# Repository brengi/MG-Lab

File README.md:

# MG-Lab
Producción del Laboratorio Mario Gattafoni

## Objetivos ##
El MG-Lab trabaja con alumnos de colegios técnicos secundarios, bajo
el régimen de práctica profesional supervisada.
Se utilizan tecnologías abiertas y se publican los resultados de cada
práctica.

## Responsables ##
El plantel estable del laboratorio esta formado por Omar Milano y Diego Brengi.

## Nombre del laboratorio ##
El laboratorio se bautiza con ese nombre en honor a Mario Gattafoni quien fue profesor
de Omar y Diego en la secundaria y en la universidad, y dedicó su vida a 
la educación técnica secundaria y universitaria.

## Grupos MG-LAB 2019

De izquierda a derecha:.

De izquierda a derecha:.

De izquierda a derecha:.

## Grupos MG-LAB 2018

De izquierda a derecha: Omar Milano, ... y Diego Brengi.

## Grupos MG-LAB 2017

De izquierda a derecha: Omar Milano, Delfina Gonzalez, Gonzalo Daniel Magdalena, Nelson Saade y Diego Brengi.

De izquierda a derecha: Diego Brengi, XX1, XX2, XX3 y Omar Milano.

## Grupos MG-LAB 2016

De izquierda a derecha: Diego Brengi, Juan Ignacio
Napolillo, Nicolas David Luna, Omar Milano y Leonel Gabriel Costa.

De izquierda a derecha: Diego Brengi, Alejandro Franco, Fernando Flores, Omar Milano y Fernando Sosa.

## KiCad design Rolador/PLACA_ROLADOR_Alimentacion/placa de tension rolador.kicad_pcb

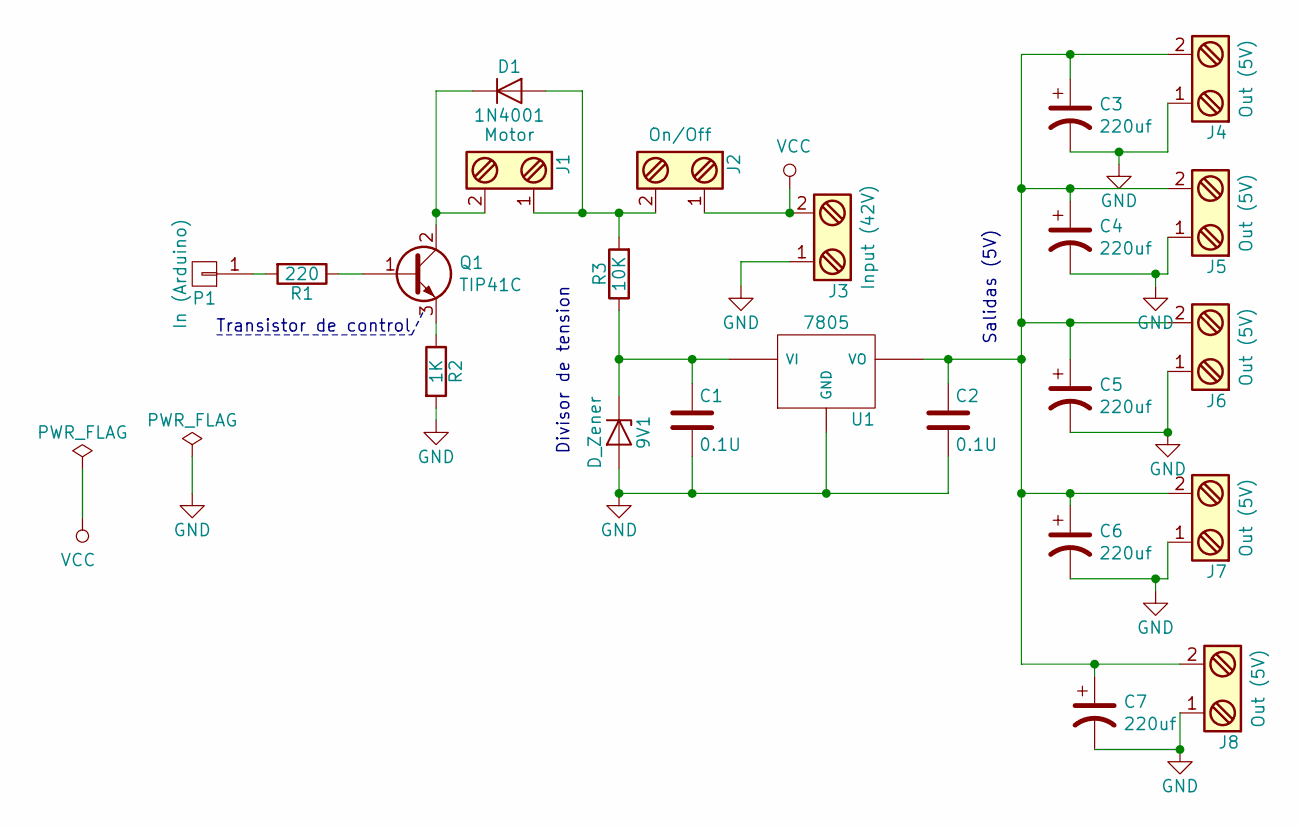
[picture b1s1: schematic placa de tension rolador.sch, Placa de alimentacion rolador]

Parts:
9V1: D_Zener; D_DO-41_SOD81_P12.70mm_Horizontal
C1, C2: 0.1U; C_Rect_L7.0mm_W6.0mm_P5.00mm
C3, C4, C5, C6, C7: 220uf; CP_Radial_D8.0mm_P3.80mm
D1: 1N4001; D_DO-41_SOD81_P12.70mm_Horizontal
J1: Motor; TerminalBlock_bornier-2_P5.08mm
J2: On/Off; TerminalBlock_bornier-2_P5.08mm
J3: Input (42V); TerminalBlock_bornier-2_P5.08mm
J4, J5, J6, J7, J8: Out (5V); TerminalBlock_bornier-2_P5.08mm
P1: In (Arduino); Pin_D0.7mm_L6.5mm_W1.8mm_FlatFork
Q1: TIP41C; TO-220-3_Vertical
R1: 220; R_Axial_DIN0207_L6.3mm_D2.5mm_P10.16mm_Horizontal
R2: 1K; R_Axial_DIN0207_L6.3mm_D2.5mm_P10.16mm_Horizontal
R3: 10K; R_Axial_DIN0207_L6.3mm_D2.5mm_P10.16mm_Horizontal
U1: 7805; TO-220-3_Vertical

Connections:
GND: 9V1.2 (A), C1.2, C2.2, C3.2, C4.2, C5.2, C6.2, C7.2, J3.1, J4.1, J5.1, J6.1, J7.1, J8.1, R2.2, U1.2 (GND)
unnamed: 9V1.1 (K), C1.1, R3.1, U1.1 (VI)
unnamed: C2.1, C3.1, C4.1, C5.1, C6.1, C7.1, J4.2, J5.2, J6.2, J7.2, J8.2, U1.3 (VO)
unnamed: D1.1 (K), J1.2, Q1.2 (C)
unnamed: D1.2 (A), J1.1, J2.2, R3.2
unnamed: P1.1, R1.2
unnamed: Q1.1 (B), R1.1
unnamed: Q1.3 (E), R2.1
VCC: J2.1, J3.2

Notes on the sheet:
Transistor de control
Divisor de tension
Salidas (5V)

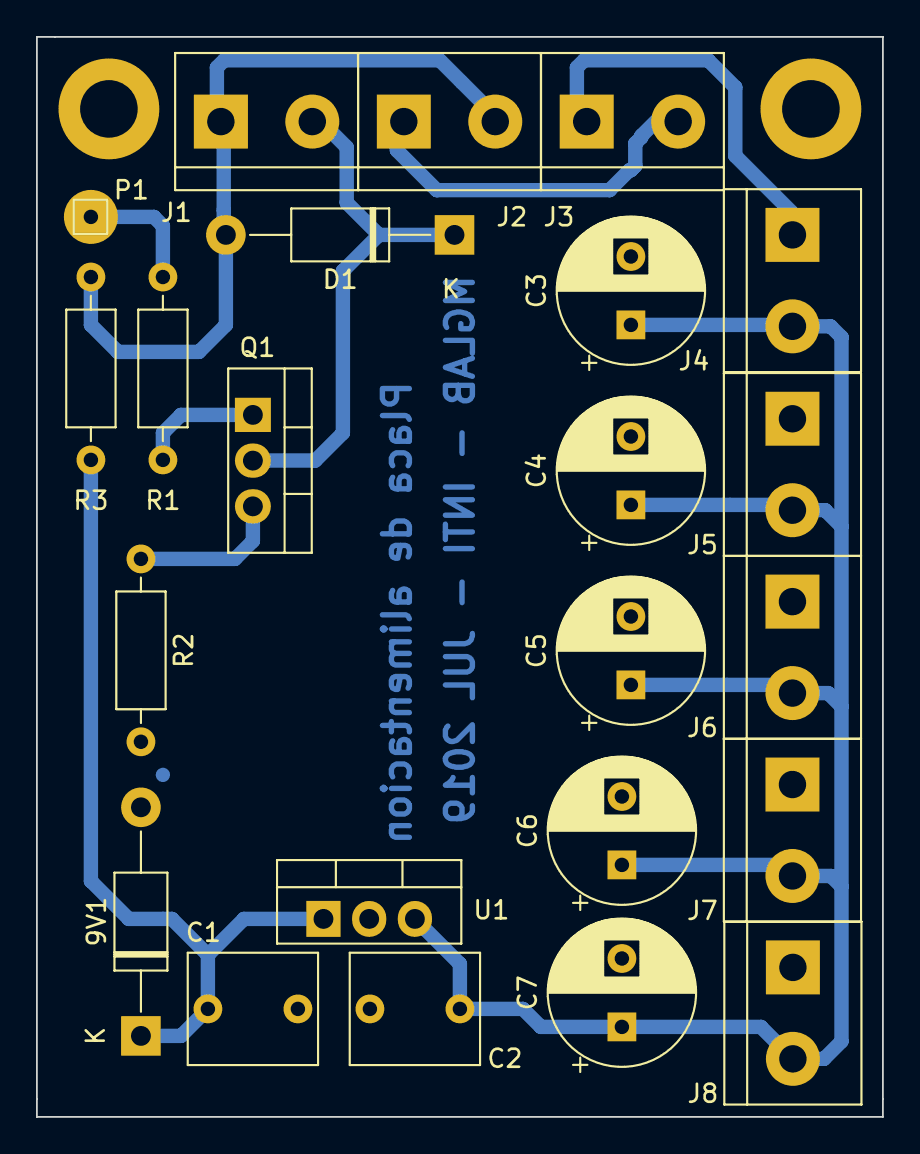
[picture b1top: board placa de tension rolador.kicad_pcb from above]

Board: 2 copper layers, 47.0 x 60.0 mm, 25 parts (0 on the bottom side), 9 nets.

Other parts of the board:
H1, H2: .; MountingHole_3.2mm_M3_DIN965_Pad

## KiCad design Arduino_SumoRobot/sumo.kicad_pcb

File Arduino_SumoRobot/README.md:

# SHIELD DE ARDUINO PARA ROBOT SUMO #
 
RESPONSABLE:  
 
## ACTIVIDAD ##
Realizar un una implementación con Arduino que permita controlar un robot 
sumo. Primero con módulos comerciales y cableado y luego si es posible, diseñar uno o 
más shields usando KiCad.
 
## PAUTAS ##
  *  Manejo de dos motores en ambos sentidos, con relés. 
  * Manejo de 4 sensores de línea infrarrojos. 
  * Entrada de dos pulsadores. 
  * Manejo de un relé o salida transistor adicional y posibilidad de manejar un servo 
(puede ser todo el mismo pin). 
  * Posibilidad de conectar uno o dos módulos de ultrasonido FR04. 
  * Considerar alimentación de 12 Volts. 
  * Considerar protecciones en el manejo de potencia: Motores, bobinas de relés y 
servos. 
  * PCBs de simple capa (que se puedan fabricar con plancha). Pueden ser varios 
shields apilables, pero que puedan trabajar todos juntos.  Puede ocupar más área
que el arduino.

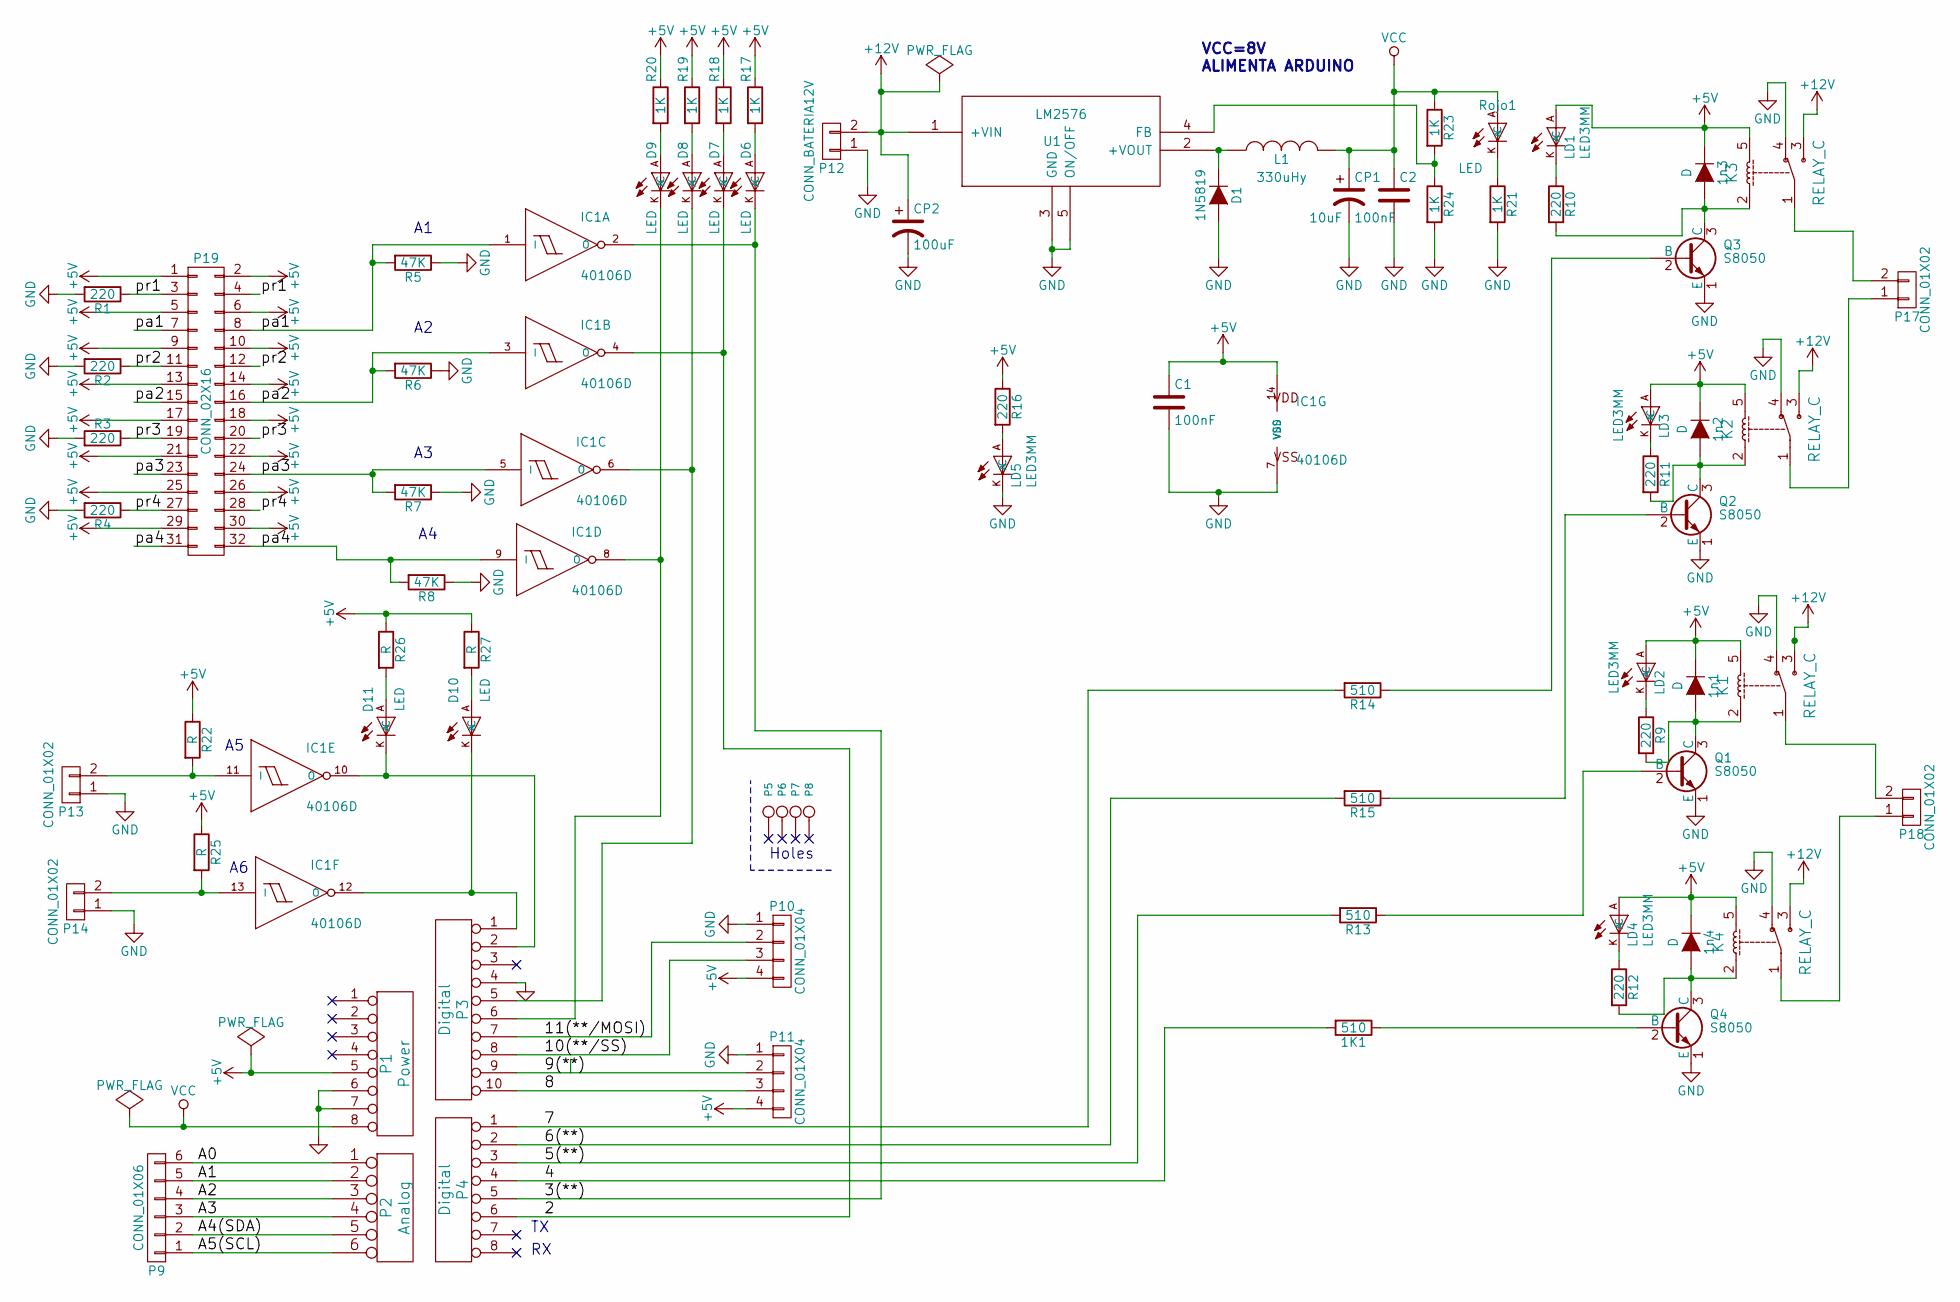
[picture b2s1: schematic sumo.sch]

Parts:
1K1: 510; Resistor_Horizontal_RM7mm
1n1, 1n2, 1n3, 1n4: D; Diode_DO-41_SOD81_Horizontal_RM10
C1, C2: 100nF; C_Rect_L7_W6_P5
CP1: 10uF; C_Radial_D6.3_L11.2_P2.5
CP2: 100uF; C_Radial_D6.3_L11.2_P2.5
D1: 1N5819; Diode_DO-41_SOD81_Horizontal_RM10
D6, D7, D8, D9, D10, D11: LED; led-LED3MM
IC1: 40106D; DIP-14_W7.62mm_LongPads
K1, K2, K3, K4: RELAY_C; Relay_SANYOU_SRD_Series_Form_C
L1: 330uHy; INDUCTOR_V
LD1, LD2, LD3, LD4, LD5: LED3MM; led-LED3MM
P1: Power; Socket_Strip_Arduino_1x08
P2: Analog; Socket_Strip_Arduino_1x06
P3: Digital; Socket_Strip_Arduino_1x10
P4: Digital; Socket_Strip_Arduino_1x08
P5, P6, P7, P8: CONN_1; Arduino_1pin
P9: CONN_01X06; Pin_Header_Straight_1x06
P10, P11: CONN_01X04; Pin_Header_Straight_1x04
P12: CONN_BATERIA12V; bornier2
P13, P14, P17, P18: CONN_01X02; bornier2
P19: CONN_02X16; Pin_Header_Straight_2x16
Q1, Q2, Q3, Q4: S8050; TO-92_Rugged
R1, R2, R3, R4, R9, R10, R11, R12, R16: 220; Resistor_Horizontal_RM7mm
R5, R6, R7, R8: 47K; Resistor_Horizontal_RM7mm
R13, R14, R15: 510; Resistor_Horizontal_RM7mm
R17, R18, R19, R20, R21, R23, R24: 1K; Resistor_Horizontal_RM7mm
R22, R25, R26, R27: R; Resistor_Horizontal_RM7mm
Rojo1: LED; led-LED3MM
U1: LM2576; TO220-51

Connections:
+5V: 1n1.1 (K), 1n2.1 (K), 1n3.1 (K), 1n4.1 (K), C1.1, IC1.14 (VDD), K1.5, K2.5, K3.5, K4.5, LD1.A, LD2.A, LD3.A, LD4.A, P1.5, P10.4, P11.4, P19.1, P19.2, P19.5, P19.6, P19.9, P19.10, P19.13, P19.14, P19.17, P19.18, P19.21, P19.22, P19.25, P19.26, P19.29, P19.30, R16.1, R17.1, R18.1, R19.1, R20.1, R22.1, R25.1, R26.1, R27.1
+12V: CP2.1, K1.3, K2.3, K3.3, K4.3, P12.2, U1.1 (+VIN)
/2: D7.K (C), IC1.4 (O), P4.6
/3(**): D6.K (C), IC1.2 (O), P4.5
/4: 1K1.2, P4.4
/5(**): P4.3, R13.2
/6(**): P4.2, R15.2
/7: P4.1, R14.2
/8: P3.10, P11.3
/9(**): P3.9, P11.2
/10(**/SS): P3.8, P10.3
/11(**/MOSI): P3.7, P10.2
/A0: P2.1, P9.6
/A1: P2.2, P9.5
/A2: P2.3, P9.4
/A3: P2.4, P9.3
/A4(SDA): P2.5, P9.2
/A5(SCL): P2.6, P9.1
/pa1: IC1.1 (I), P19.7, P19.8, R5.2
/pa2: IC1.3 (I), P19.15, P19.16, R6.2
/pa3: IC1.5 (I), P19.23, P19.24, R7.2
/pa4: IC1.9 (I), P19.31, P19.32, R8.2
/pr1: P19.3, P19.4, R1.1
/pr2: P19.11, P19.12, R2.1
/pr3: P19.19, P19.20, R3.1
/pr4: P19.27, P19.28, R4.1
GND: C1.2, C2.2, CP1.2, CP2.2, D1.2 (A), IC1.7 (VSS), K1.4, K2.4, K3.4, K4.4, LD5.K (C), P1.6, P1.7, P3.4, P10.1, P11.1, P12.1, P13.1, P14.1, Q1.1 (E), Q2.1 (E), Q3.1 (E), Q4.1 (E), R1.2, R2.2, R3.2, R4.2, R5.1, R6.1, R7.1, R8.1, R21.2, R24.2, U1.3 (GND), U1.5 (ON/OFF)
unnamed: 1K1.1, Q4.2 (B)
unnamed: 1n1.2 (A), K1.2, Q1.3 (C), R9.2
unnamed: 1n2.2 (A), K2.2, Q2.3 (C), R11.2
unnamed: 1n3.2 (A), K3.2, Q3.3 (C), R10.2
unnamed: 1n4.2 (A), K4.2, Q4.3 (C), R12.2
unnamed: D1.1 (K), L1.1, U1.2 (+VOUT)
unnamed: D6.A, R17.2
unnamed: D7.A, R18.2
unnamed: D8.A, R19.2
unnamed: D8.K (C), IC1.6 (O), P3.5
unnamed: D9.A, R20.2
unnamed: D9.K (C), IC1.8 (O), P3.6
unnamed: D10.A, R27.2
unnamed: D10.K (C), IC1.12 (O), P3.1
unnamed: D11.A, R26.2
unnamed: D11.K (C), IC1.10 (O), P3.2
unnamed: IC1.11 (I), P13.2, R22.2
unnamed: IC1.13 (I), P14.2, R25.2
unnamed: K1.1, P18.2
unnamed: K2.1, P17.1
unnamed: K3.1, P17.2
unnamed: K4.1, P18.1
unnamed: LD1.K (C), R10.1
unnamed: LD2.K (C), R9.1
unnamed: LD3.K (C), R11.1
unnamed: LD4.K (C), R12.1
unnamed: LD5.A, R16.2
unnamed: Q1.2 (B), R13.1
unnamed: Q2.2 (B), R15.1
unnamed: Q3.2 (B), R14.1
unnamed: R21.1, Rojo1.K (C)
unnamed: R23.2, R24.1, U1.4 (FB)
VCC: C2.1, CP1.1, L1.2, P1.8, R23.1, Rojo1.A

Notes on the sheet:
Holes
VCC=8V ALIMENTA ARDUINO

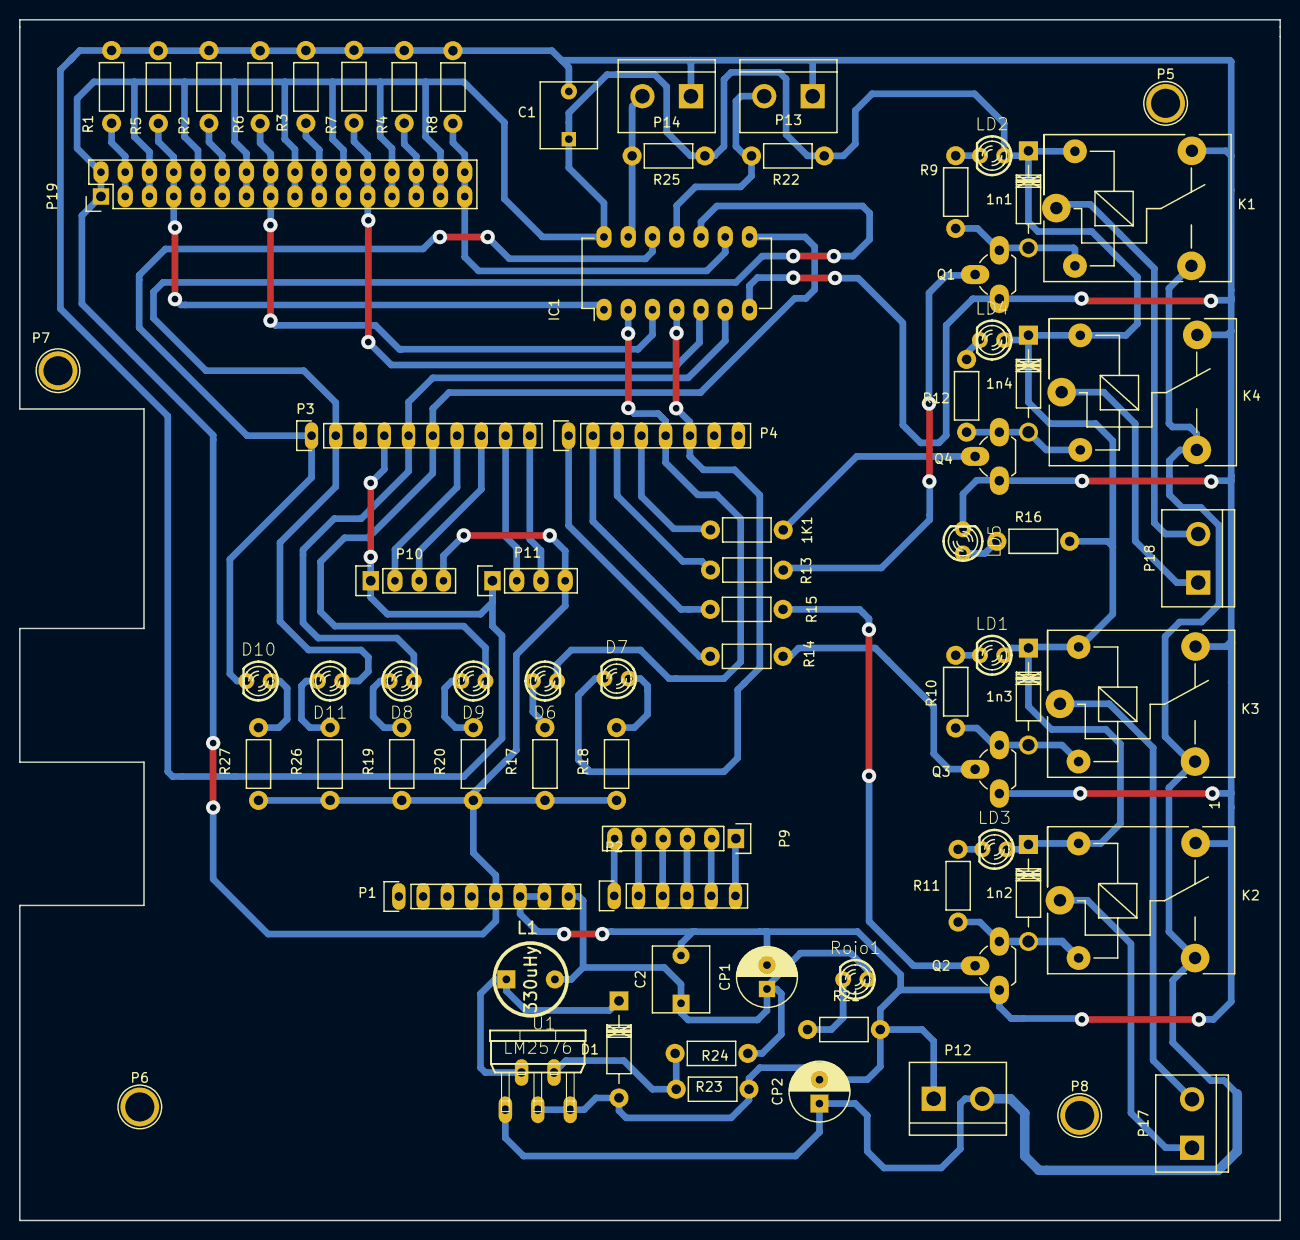
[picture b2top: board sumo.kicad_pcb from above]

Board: 2 copper layers, 132.0 x 125.8 mm, 77 parts (0 on the bottom side), 60 nets.

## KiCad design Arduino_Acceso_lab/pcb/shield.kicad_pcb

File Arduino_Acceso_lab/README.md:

# ARDUINO PARA  MONITOREO DE USO DE INSTALACIONES #
 
RESPONSABLE: Costa Leonel
 
## ACTIVIDAD ##
Utilizar un Arduino para ayudar a regular, monitorear y organizar el uso de un laboratorio 
de electrónica.
 
## PAUTAS ##
  * Lectura de sensor de presencia infrarrojo. Uno o preferentemente dos para distinguir 
zonas. ZONA 1:  podría marcar entrada/salida del recinto (suena siempre) y ZONA 2 
uso y permanencia en el laboratorio.  
  * Manejo de una luz que se vea a distancia. La luz indica que se ha detectado 
presencia en alguna zona y tiene temporización al apagado. 
  * Manejo de bocina/buzzer para indicar entrada/salida del recinto o ZONA 2 sin tarjeta. 
  *  Manejo de tarjeta NFC. Dejando la tarjeta en el lector, la alarma ZONA 2 no suena. 
  * Considerar el gabinete para el arduino con el sensor NFC. Se puede imprimir con 
impresora 3D. 
  * Si hay tiempo. Uso del  RTC para saber hora y fecha de los eventos. 
  * SI hay tiempo. Uso de Wifi. Analizar si es posible un sistema de alta y baja de 
tarjetas o consulta de registro de uso.

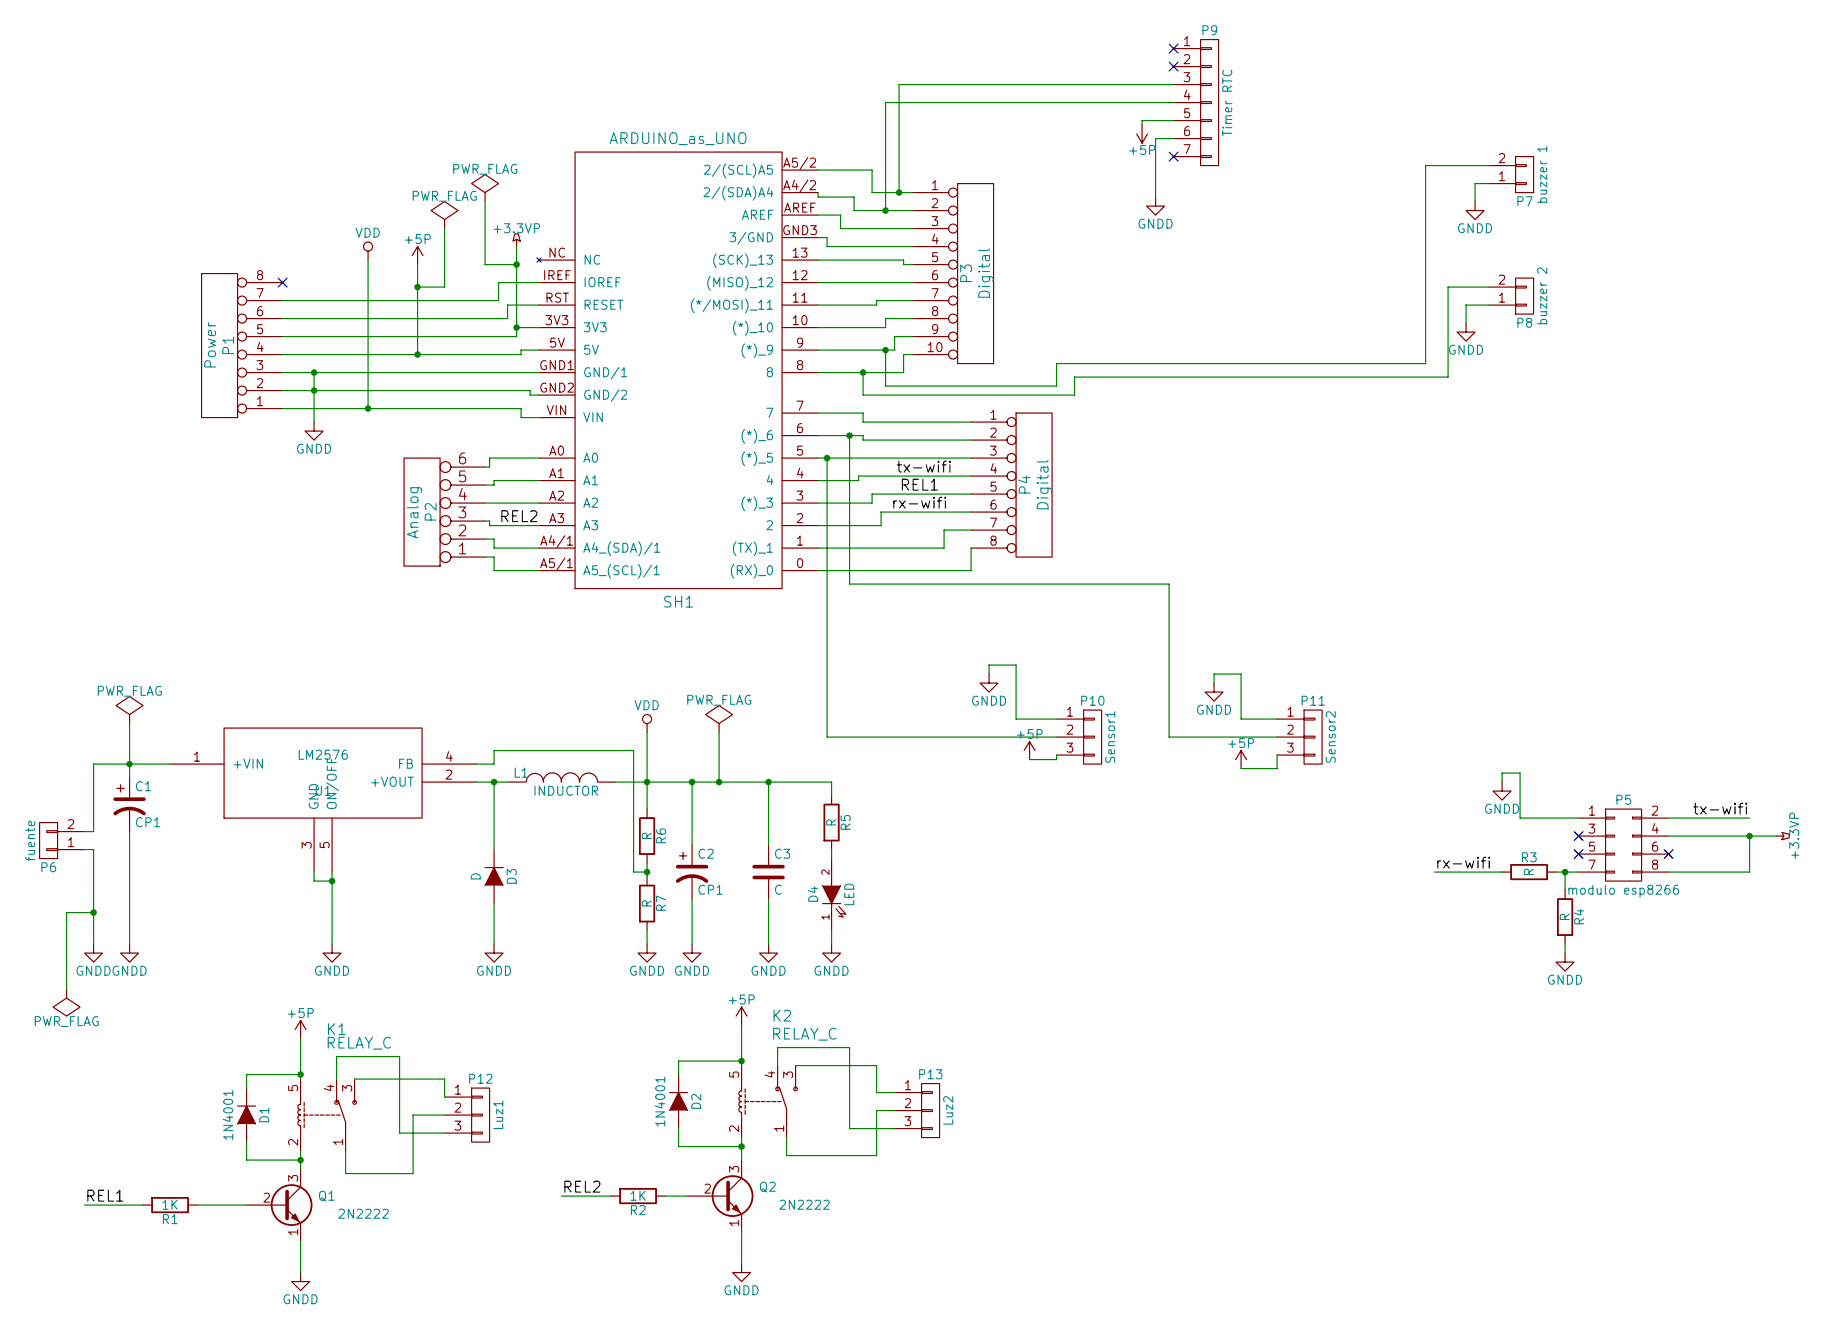
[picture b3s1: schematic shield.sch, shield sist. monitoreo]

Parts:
C1, C2: CP1; C_Rect_L7.5_W6.5_P5
C3: C; C_Rect_L7.5_W6.5_P5
D1, D2: 1N4001; Diode_DO-35_SOD27_Horizontal_RM10
D3: D; Diode_DO-35_SOD27_Horizontal_RM10
D4: LED; LED-3MM
K1, K2: RELAY_C; Relay_C
L1: INDUCTOR; INDUCTOR_V
P1: Power; Socket_Strip_Straight_1x08
P2: Analog; Socket_Strip_Straight_1x06
P3: Digital; Socket_Strip_Straight_1x10
P4: Digital; Socket_Strip_Straight_1x08
P5: modulo esp8266; Socket_Strip_Straight_2x04
P6: fuente; bornier2
P7: buzzer 1; Pin_Header_Straight_1x02
P8: buzzer 2; Pin_Header_Straight_1x02
P9: Timer RTC; Socket_Strip_Straight_1x07
P10: Sensor1; BORNERA3
P11: Sensor2; BORNERA3
P12: Luz1; BORNERA3
P13: Luz2; BORNERA3
Q1, Q2: 2N2222; TO92-L21
R1, R2: 1K; Resistor_Horizontal_RM7mm
R3, R4, R5, R6, R7: R; Resistor_Horizontal_RM7mm
SH1: ARDUINO_as_UNO; ARDUINO_as_UNO_R3
U1: LM2576; Pentawatt_Neutral_Staggered_Verical_TO220-5-T05D

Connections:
+3.3VP: P1.5, P5.4, P5.8, SH1.3V3
+5P: D1.1 (K), D2.1 (K), K1.5, K2.5, P1.4, P9.5, P10.3, P11.3, SH1.5V
/REL1: P4.5, R1.2, SH1.3 ((*)_3)
/REL2: P2.3, R2.2, SH1.A3
/rx-wifi: P4.6, R3.1, SH1.2
/tx-wifi: P4.4, P5.2, SH1.4
GNDD: C1.2, C2.2, C3.2, D3.2 (A), D4.1 (K), P1.2, P1.3, P5.1, P6.1, P7.1, P8.1, P9.6, P10.1, P11.1, Q1.1 (E), Q2.1 (E), R4.2, R7.2, SH1.GND1 (GND/1), SH1.GND2 (GND/2), U1.3 (GND), U1.5 (ON/OFF)
unnamed: C1.1, P6.2, U1.1 (+VIN)
unnamed: D1.2 (A), K1.2, Q1.3 (C)
unnamed: D2.2 (A), K2.2, Q2.3 (C)
unnamed: D3.1 (K), L1.1, U1.2 (+VOUT)
unnamed: D4.2 (A), R5.2
unnamed: K1.1, P12.2
unnamed: K1.3, P12.1
unnamed: K1.4, P12.3
unnamed: K2.1, P13.2
unnamed: K2.3, P13.1
unnamed: K2.4, P13.3
unnamed: P1.6, SH1.RST (RESET)
unnamed: P1.7, SH1.IREF (IOREF)
unnamed: P2.1, SH1.A5/1 (A5_(SCL)/1)
unnamed: P2.2, SH1.A4/1 (A4_(SDA)/1)
unnamed: P2.4, SH1.A2
unnamed: P2.5, SH1.A1
unnamed: P2.6, SH1.A0
unnamed: P3.1, P9.3, SH1.A5/2 (2/(SCL)A5)
unnamed: P3.2, P9.4, SH1.A4/2 (2/(SDA)A4)
unnamed: P3.3, SH1.AREF
unnamed: P3.4, SH1.GND3 (3/GND)
unnamed: P3.5, SH1.13 ((SCK)_13)
unnamed: P3.6, SH1.12 ((MISO)_12)
unnamed: P3.7, SH1.11 ((*/MOSI)_11)
unnamed: P3.8, SH1.10 ((*)_10)
unnamed: P3.9, P7.2, SH1.9 ((*)_9)
unnamed: P3.10, P8.2, SH1.8
unnamed: P4.1, SH1.7
unnamed: P4.7, SH1.1 ((TX)_1)
unnamed: P4.8, SH1.0 ((RX)_0)
unnamed: P5.7, R3.2, R4.1
unnamed: P4.3, P10.2, SH1.5 ((*)_5)
unnamed: P4.2, P11.2, SH1.6 ((*)_6)
unnamed: Q1.2 (B), R1.1
unnamed: Q2.2 (B), R2.1
unnamed: R6.2, R7.1, U1.4 (FB)
VDD: C2.1, C3.1, L1.2, P1.1, R5.1, R6.1, SH1.VIN

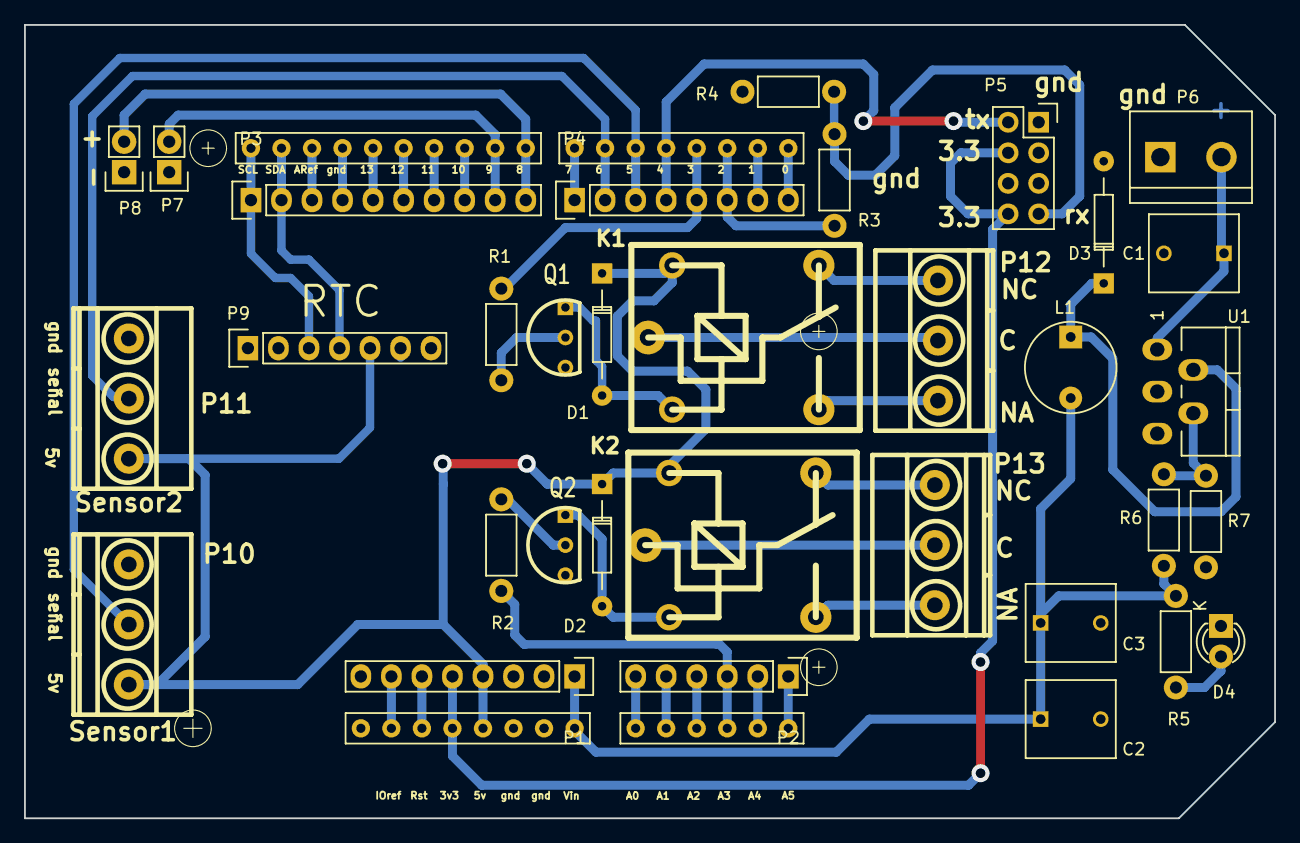
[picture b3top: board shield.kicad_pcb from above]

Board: 2 copper layers, 104.0 x 66.0 mm, 34 parts (0 on the bottom side), 45 nets.

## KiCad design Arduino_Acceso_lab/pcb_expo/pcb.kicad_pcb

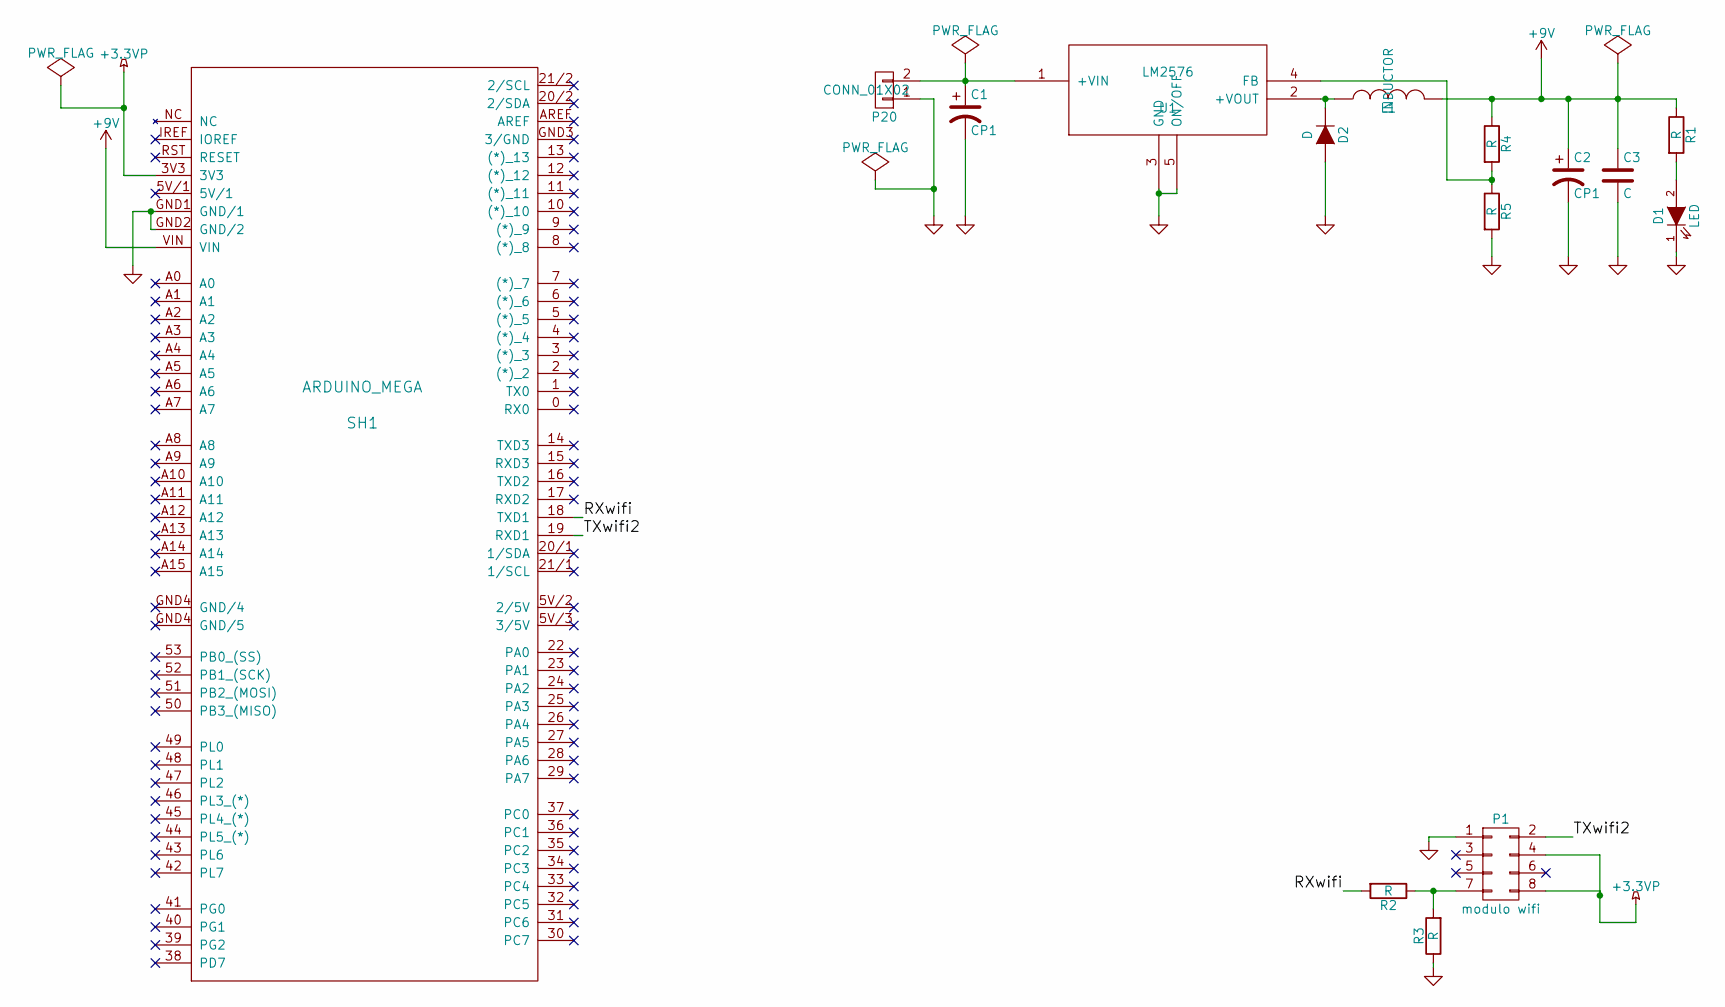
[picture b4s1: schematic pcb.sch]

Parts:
C1, C2: CP1; C_Rect_L7.5_W6.5_P5
C3: C; C_Rect_L7.5_W6.5_P5
D1: LED; LED-5MM
D2: D; Diode_DO-35_SOD27_Horizontal_RM10
L1: INDUCTOR; INDUCTOR_V
P1: modulo wifi; Socket_Strip_Straight_2x04
P20: CONN_01X02; bornier2
R1, R2, R3, R4, R5: R; Resistor_Horizontal_RM10mm
SH1: ARDUINO_MEGA; ARDUINO_MEGA_2560_R3_ELL
U1: LM2576; Pentawatt_Neutral_Staggered_Verical_TO220-5-T05D

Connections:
+3.3VP: P1.4, P1.8, SH1.3V3
+9V: C2.1, C3.1, L1.2, R1.1, R4.1, SH1.VIN
/RXwifi: R2.2, SH1.18 (TXD1)
/TXwifi2: P1.2, SH1.19 (RXD1)
GND: C1.2, C2.2, C3.2, D1.1 (K), D2.2 (A), P1.1, P20.1, R3.1, R5.2, SH1.GND1 (GND/1), SH1.GND2 (GND/2), U1.3 (GND), U1.5 (ON/OFF)
unnamed: C1.1, P20.2, U1.1 (+VIN)
unnamed: D1.2 (A), R1.2
unnamed: D2.1 (K), L1.1, U1.2 (+VOUT)
unnamed: P1.7, R2.1, R3.2
unnamed: R4.2, R5.1, U1.4 (FB)

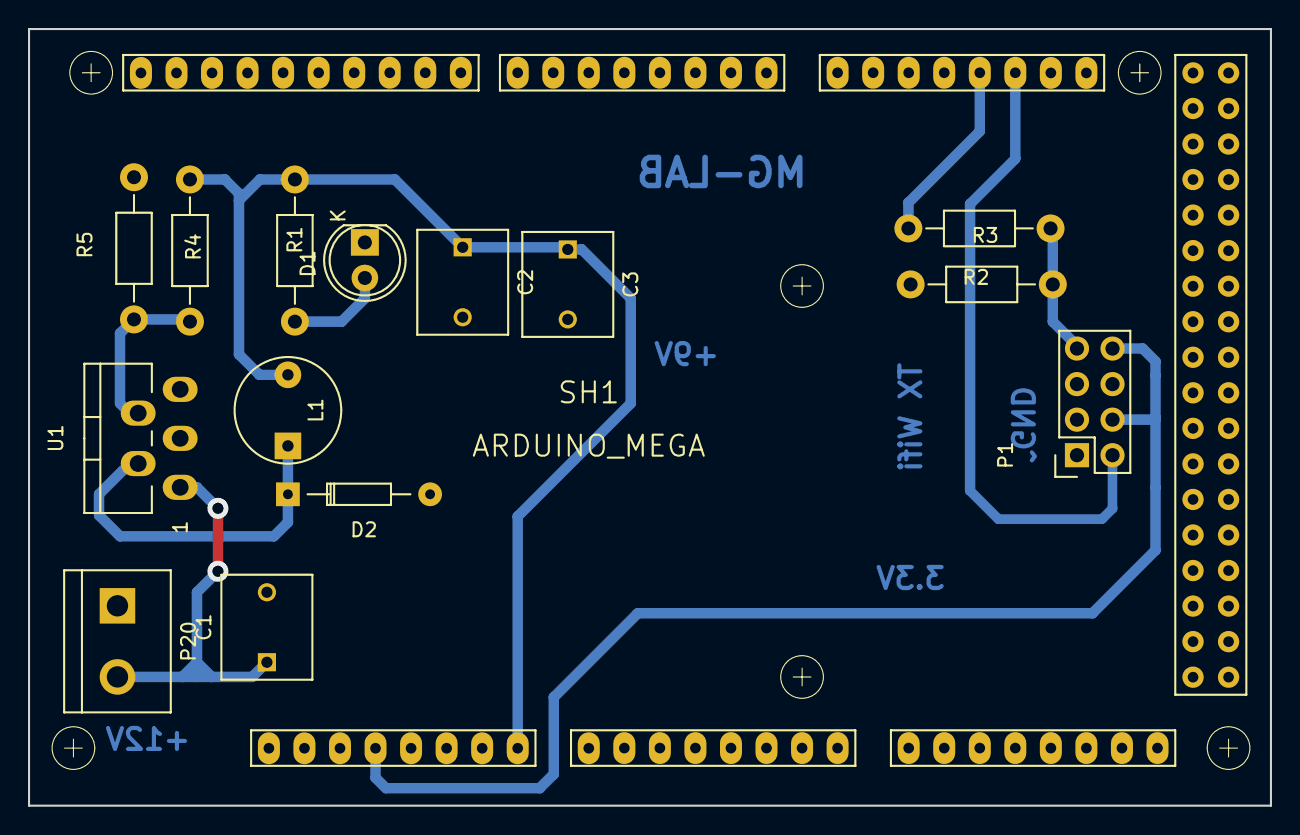
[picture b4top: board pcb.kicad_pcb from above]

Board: 2 copper layers, 88.8 x 55.5 mm, 15 parts (0 on the bottom side), 10 nets.

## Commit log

2016-07-21 Agrego el trabajo de aplicación para acceso a laboratorio.
2016-07-21 Ordenamiento de bibliotecas y footprints.
2016-07-21 Agrego archivos del proyecto Sumo Robot con Arduino.
2016-07-21 Reorganizo bibliotecas del Arduino_SumoRobot.
2016-07-21 Agrego los archivos del Poncho Sumo Robot.
2016-07-21 Reorganizo bibliotecas en esquemático y PCB. Reparo señal de 12V. Agrego Footprints. Coloco plantilla EDU-CIAA. Reparo asociación conector EDU-CIAA en sch y pcb.
2016-07-21 Agrego tracking de archivo netlist.
2016-07-21 Agrego biblioteca de simbolos.
2016-07-21 Configuro directorios de impresión.
2016-07-21 Correcciones propuestas al Poncho SumoRobot.
2016-07-21 Modificaciones propuestas al esquemático de acceso_lab.
2016-07-21 Sugerencias del esquemático del Arduino_sumo.
2016-07-21 Agrego contenido al README.
2016-07-21 Agrego los README,md de cada proyecto.
2016-07-21 Corrijo faltante de +5V y quito biblioteca power del Acceso_lab.
2016-08-18 Actualizo trabajo del Poncho Sumo Robot.
2016-08-23 Agrego avances y algunas correcciones propias: etiquetas 5V, serigrafía, prolijidad.
2016-08-24 Corrijo Dip16 a Dip14, Corrijo net 12V, Limpio placa para rerutear.
2016-08-24 Correcciones varias, serigrafía, ruteo, borneras, puentes, planos, etc.
2016-08-24 muevo una pista para achicar el borde.
2016-08-24 Actualizo pcb del Arduino Acceso lab.
2016-08-24 Quito bibliotecas símbolos innecesarias.
2016-09-08 Borro archivo.
2016-09-08 Arduino Acceso Lab. Ultimas modificaciones al PCB.
2016-09-08 EDU-CIAA Poncho Sumo Robot. Ultimos cambios de vías y puentes para simple faz.
2016-09-08 Arduino_Acceso_lab/firmware ultimos agregados.
2016-09-08 Agrego prueba del shield de Sumo Robot para Arduino.
2016-11-02 Agrego huellas y símbolos nuevos.
2016-11-02 Primer borrador de la versión 2 de la placa Arduino Sumo.
2016-11-02 Cambios en el esquemático y asignación de huellas dentro del proyecto.
2016-11-02 Agrego huellas adicionales al arduino-sumo.
2016-11-02 Cambios significativos en el PCB arduino sumo. desruteo. reorganización de componentes. reglas de diseño.
2016-11-02 Arduino Sumo. Cambio todos los leds a 3mm porque había una mezcla.
2016-11-03 Anoto correcciones al Poncho Sumo.
2016-11-08 Agrego version Expo del módulo wifi con Arduino Mega.
2016-11-08 Versión corregida por DJB del Shield Wifi para Arduini Mega.
2016-11-08 Detalles Arduino Mega Wifi Shield.
2016-11-14 Agregado de fotos grupales.
2016-11-14 Agrego fotos al README.
2016-11-14 Agrego algunos nombres.
2016-11-14 Agrego mejoras al shield para acceso lab.
2016-11-14 Nuevo PCB.
2016-11-14 Detalles pcb acceso arduino lab.
2016-11-14 borro shield-rescue.lib
2016-11-14 Agrego power flags y quito lib rescue.
2016-12-20 Agrego reporte de Acceso Lab Grupo 2.
2016-12-20 Agrego avances en el PCB de Acceso Lab.
2016-12-20 Agrego mejoras al Arduino Sumo Robot realizadas por el Grupo II de 2016.
2017-06-07 typo.
2017-06-08 Agregados.
2017-06-08 Agrego foto grupal.
2017-06-08 Agrego apellidos grupo 3.
2017-12-06 Agrego el anteúltimo grupo.
2017-12-06 Correcciones de año.
2019-07-31 Agrego placa rolador con modificaciones DJB
2019-08-07 Agrego foto 2018.
2019-08-07 Agrego fotos grupales 2019.
2019-10-07 Se agrega el directorio Boton_Auxilio con lo desarrollado en la turoria en el manejo del ESP32 y el servicio de internet IFTTT, junto con el diagrama en bloques basic del proyecto.
2019-10-07 se eliminar los archivos .zip del directorio ESP32_Module/Libreries
